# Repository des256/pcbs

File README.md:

# PCBs

Making electronics as well

## Prerequisites

KiCad 10.0
install plugin: impart GUI for KiCad
install plugin: Fabrication Toolkit
install plugin: wDark Theme
install repository: CD_FER's KiCad repository (https://raw.githubusercontent.com/CDFER/cd_fer-kicad-repository/main/repository.json)
install plugin: JLCPCB: KiCad Library

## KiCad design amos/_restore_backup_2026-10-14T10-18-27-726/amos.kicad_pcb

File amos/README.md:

# Amos

Jetson helper board (USB3 + 12V RS-485 Servo + 5V UART Servo)

Input Power: 19V laptop
Output Power: 19V jetson + 12V (10A..20A) servo + 5V (5A..10A) servo + 5V (5A) USB

Upstream USB Hub: USB3-C
Downstream USB Hub: 3x USB3-A + 1x internal to CH344Q

each servo bus either 12V 4-pin RS-485 or 5V 3-pin UART
selectable with DIP

## Schematic Sheets

2: Main Power + Jetson
3: Buck 12V 10A..20A
4: Buck 5V 5A..10A
5: Buck 5V USB
6: Buck 3V3 + 1V1
7: USB HUB
8: CH344Q
9: Servo A
10: Servo B
11: Servo C
12: Servo D
13: USB A
14: USB B
15: USB C

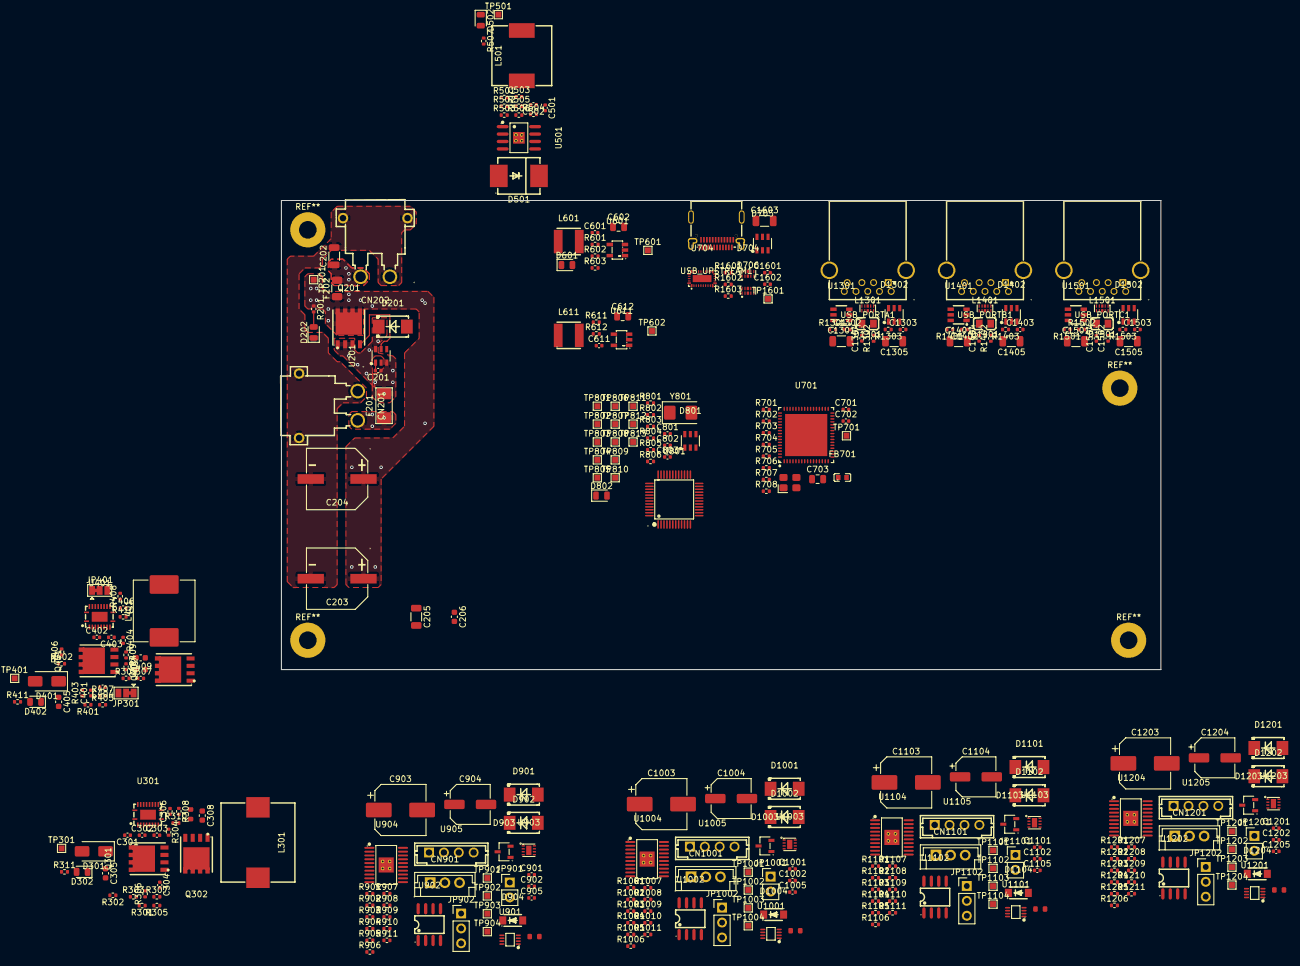
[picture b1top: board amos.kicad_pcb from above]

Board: 4 copper layers, 150.0 x 80.0 mm, 327 parts (0 on the bottom side), 216 nets.

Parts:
C201, C307, C407, C503, C803, C901, C902, C905, C1001, C1002, C1005, C1101, C1102, C1105, C1201, C1202, C1205, C1302, C1303, C1304, C1402, C1403, C1404, C1502, C1503, C1504, C1601, C1602: 100nF; C_0402_1005Metric
C202, C205: 10uF 50V; C_1206_3216Metric
C203, C204: 470uF 35V; CAP-SMD_BD10.0-L10.3-W10.3-LS11.3-FD
C206: 100nF 100V; C_0603_1608Metric
C301: 33nF; C_0402_1005Metric
C302, C502: 47pF; C_0402_1005Metric
C303: 3.3nF; C_0402_1005Metric
C304: 680pF; C_0402_1005Metric
C305, C405: 2.2uF; C_0603_1608Metric
C306: 10pF; C_0402_1005Metric
C308, C409: 100pF; C_0603_1608Metric
C401: 47nF; C_0402_1005Metric
C402: 150pF; C_0402_1005Metric
C403, C501: 4.7nF; C_0402_1005Metric
C404: 1.8nF; C_0402_1005Metric
C406: 15pF; C_0402_1005Metric
C601, C611: 6.8pF; C_0402_1005Metric
C602, C612: 22uF; C_0805_2012Metric
C701, C702: 30pF; C_0402_1005Metric
C703: 10uF; C_0805_2012Metric
C801, C802: 33pF; C_0402_1005Metric
C903, C1003, C1103, C1203: 470uF 25V; CP_Elec_8x10.5
C904, C1004, C1104, C1204: 470uF 10V; CP_Elec_6.3x7.7
C1301, C1401, C1501: 47uF 10V; C_1206_3216Metric
C1305, C1405, C1505, C1603: 1nF 2kV; C_1206_3216Metric
CN201: 19V INPUT; CONN-TH_XT30PW-M
CN202: 19V JETSON; CONN-TH_XT30PW-M
CN901, CN1001, CN1101, CN1201: B3B-EH-A; CONN-TH_B3B-EH-A-LF-SN
D201: SMBJ24A_C908801; SMB_L4.4-W3.6-LS5.3-RD
D202, D302, D402, D502, D601: LED Green; LED_0805_2012Metric
D301, D401: SS14; D_SMA
D501: B560C; SMC_L7.1-W6.2-LS8.1-RD
D704, D706, D1301, D1401, D1501: TPD4E05U06DQAR_C138714; USON-10_L2.5-W1.0-P0.50-BL
D705, D801, D1302, D1402, D1502: USBLC6-2SC6; SOT-23-6_L2.9-W1.6-P0.95-LS2.8-BL
D802: LED Yellow; LED_0805_2012Metric
D901, D1001, D1101, D1201: SMBJ13A; SMB_L4.4-W3.6-LS5.3-RD
D902, D1002, D1102, D1202: SMBJ6.0A; SMB_L4.4-W3.6-LS5.3-RD
D903, D1003, D1103, D1203: PSM712-LF-T7; SOT-23-3_L3.0-W1.7-P0.95-LS2.9-BR
D904, D1004, D1104, D1204: SMF5.0A; SOD-123FL_L2.8-W1.9-LS3.7-RD
F201: 15A T 2410; Fuse_2410_6125Metric
F202: 4A T 1206; Fuse_1206_3216Metric
FB701: BLM18PG221SN1D; L0603
JP301, JP401: SYNCIN GND OR PGOOD; SolderJumper-3_P1.3mm_Bridged12_Pad1.0x1.5mm
JP901, JP1001, JP1101, JP1201: RETRY; PinHeader_1x02_P2.54mm_Vertical
JP902, JP1002, JP1102, JP1202: 12=RS-485, 23=TTL; PinHeader_1x03_P2.54mm_Vertical
L301: 4.7uH 20A; IND-SMD_L13.5-W12.6
L401: 3.3uH 18A; L_Vishay_IHLP-4040
L501: 7.2uH 6A; IND-SMD_L10.2-W10.2_7447798720
L601, L611: 2.2uH 3.4A; IND-SMD_L4.0-W4.0_LQH44PN2R2MP0L
L1301, L1401, L1501: BLM21PG221SN1D; L0805
Q201, Q301, Q302, Q401, Q402: CSD18532Q5B; SON-8_L5.0-W6.0-P1.27-BL-1
R201, R703, R705, R706, R707, R708, R801, R911, R1011, R1111, R1211, R1301, R1401, R1501: 10k; R_0402_1005Metric
R301, R401, R611: 82k; R_0402_1005Metric
R302, R402: 7.5k; R_0402_1005Metric
R303: 24.9k; R_0402_1005Metric
R304: 15k; R_0402_1005Metric
R305: 2.37k; R_0402_1005Metric
R306: 200; R_0402_1005Metric
R307: 33.2k; R_0402_1005Metric
R308, R408: 20k; R_0402_1005Metric
R309, R409: 2.2; R_0402_1005Metric
R310: 240; R_0402_1005Metric
R311, R803, R804, R805, R806: 4.7k; R_0402_1005Metric
R312, R413: 2.2; R_0603
R403: 49.9; R_0402_1005Metric
R404: 11k; R_0402_1005Metric
R405: 23.2k; R_0402_1005Metric
R406, R411, R507, R603, R802: 1k; R_0402_1005Metric
R407: 4.42k; R_0402_1005Metric
R410: 150; R_0402_1005Metric
R501: 442k; R_0402_1005Metric
R502, R704: 90.9k; R_0402_1005Metric
R503: 243k; R_0402_1005Metric
R504, R1302, R1402, R1502: 16.9k; R_0402_1005Metric
R505: 53.6k; R_0402_1005Metric
R506: 10.2k; R_0402_1005Metric
R601: 453k; R_0402_1005Metric
R602, R612, R904, R906, R908, R909, R1004, R1006, R1008, R1009, R1104, R1106, R1108, R1109, R1204, R1206, R1208, R1209: 100k; R_0402_1005Metric
R701: 9.53k; R_0402_1005Metric
R702, R1303, R1403, R1503, R1602: 1M; R_0402_1005Metric
R901, R1001, R1101, R1201: 18.2k; R_0402_1005Metric
R902, R1002, R1102, R1202: 249k; R_0402_1005Metric
R903, R1003, R1103, R1203: 20.5k; R_0402_1005Metric
R905, R1005, R1105, R1205: 4.02k; R_0402_1005Metric
R907, R1007, R1107, R1207: 1.02k; R_0402_1005Metric
R910, R1010, R1110, R1210: 22; R_0402_1005Metric
R912, R1012, R1112, R1212: 120; R_0603
R1601: 910k; R_0402_1005Metric
R1603: 200k; R_0402_1005Metric
TP201: +19V; TestPoint_Pad_1.0x1.0mm
TP301: +12V_SERVO; TestPoint_Pad_1.0x1.0mm
TP401: +5V_SERVO; TestPoint_Pad_1.0x1.0mm
TP501: +5V_USB; TestPoint_Pad_1.0x1.0mm
TP601: +3V3; TestPoint_Pad_1.0x1.0mm
TP602: +1V1; TestPoint_Pad_1.0x1.0mm
TP701: GRSTz; TestPoint_Pad_1.0x1.0mm
TP801: RESET; TestPoint_Pad_1.0x1.0mm
TP802: SERVOB_TXD; TestPoint_Pad_1.0x1.0mm
TP803: SERVOB_RXD; TestPoint_Pad_1.0x1.0mm
TP804: SERVOB_TNOW; TestPoint_Pad_1.0x1.0mm
TP805: SERVOC_TXD; TestPoint_Pad_1.0x1.0mm
TP806: SERVOC_RXD; TestPoint_Pad_1.0x1.0mm
TP807: SERVOC_TNOW; TestPoint_Pad_1.0x1.0mm
TP808: SERVOD_TXD; TestPoint_Pad_1.0x1.0mm
TP809: SERVOD_RXD; TestPoint_Pad_1.0x1.0mm
TP810: SERVOD_TNOW; TestPoint_Pad_1.0x1.0mm
TP811: SERVOA_TXD; TestPoint_Pad_1.0x1.0mm
TP812: SERVOA_RXD; TestPoint_Pad_1.0x1.0mm
TP813: SERVOA_TNOW; TestPoint_Pad_1.0x1.0mm
TP901, TP1001, TP1101, TP1201: SHDN; TestPoint_Pad_1.0x1.0mm
TP902, TP1002, TP1102, TP1202: RS485 A; TestPoint_Pad_1.0x1.0mm
TP903, TP1003, TP1103, TP1203: TTL DATA; TestPoint_Pad_1.0x1.0mm
TP904, TP1004, TP1104, TP1204: RS485 B; TestPoint_Pad_1.0x1.0mm
TP1601: DIR; TestPoint_Pad_1.0x1.0mm
U201: LM74700QDBVTQ1; SOT-23-6_L2.9-W1.6-P0.95-LS2.8-TL
U301, U401: LM5145RGYR; VQFN-20_L4.5-W3.5-P0.50-BL-EP
U501: TPS54560DDAR; SOIC-8_L5.0-W4.0-P1.27-LS6.0-BL-EP2.0
U601, U611: TLV62569DBVR; SOT-23-5_L3.0-W1.7-P0.95-LS2.8-BR
U701: TUSB8041IRGCR; QFN-64_L9.0-W9.0-P0.50-BL-EP7.2
U704: HD3SS3220RNHR; WQFN-30_L4.5-W2.5-P0.4-BL-EP
U801: CH344Q_C2988084; LQFP-48_L7.0-W7.0-P0.50-LS9.0-BL
U901, U1001, U1101, U1201: SN74LVC2G241DCU; VSSOP-8_L2.3-W2.0-P0.50-LS3.1-BR
U902, U1002, U1102, U1202: SP3485EN-L/TR; SOIC-8_L5.0-W4.0-P1.27-LS6.0-BL
U903, U1003, U1103, U1203: TPS259531DSGR; WSON-8_L2.0-W2.0-P0.50-TL-EP
U904, U1004, U1104, U1204: TPS16630PWPR; HTSSOP-20_L6.5-W4.4-P0.65-LS6.4-TL-EP2.58
U905, U1005, U1105, U1205: B4B-EH-A; CONN-TH_B4B-EH-A-LF-SN
U1301, U1401, U1501: TPS2553DBVR; SOT-23-6_L2.9-W1.6-P0.95-LS2.8-BR
USB_PORTA1: HC-ST-003-01-J; USB-3.0-A-TH_HC-ST-003-01-Z
USB_PORTB1: HC-ST-003-01-J; USB-3.0-A-TH_HC-ST-003-01-Z
USB_PORTC1: HC-ST-003-01-J; USB-3.0-A-TH_HC-ST-003-01-Z
USB_UPSTREAM1: TYPE-C 24P QT; USB-C-SMD_TYPE-C-24P-QT
Y701: 24MHz 18pF; OSC-SMD_4P-L3.2-W2.5-BL
Y801: 8MHz 20pF; Crystal_SMD_5032-2Pin_5.0x3.2mm

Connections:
+1V1: C611.2, C612.1, FB701.2, L611.2, R611.2, TP602.1 (1_1), U701.5 (VDD), U701.8 (VDD), U701.13 (VDD), U701.21 (VDD), U701.28 (VDD), U701.31 (VDD)
+3V3: C601.2, C602.1, D801.5, L601.2, R601.2, R603.1, R703.2, R706.1, R707.2, R708.2, R801.1, R802.2, R908.1, R909.1, R911.2, R1008.1, R1009.1, R1011.2, R1108.1, R1109.1, R1111.2, R1208.1, R1209.1, R1211.2, R1301.2, R1401.2, R1501.2, R1601.1, R1603.1, TP601.1 (1_1), U701.16 (VDD33), U701.34 (VDD33), U701.52 (VDD33), U701.63 (VDD33), U704.8 (VCC33), U801.9 (VCC), U801.24 (VCC), U801.36 (VCC), U801.48 (VCC), U901.8 (VCC), U902.8 (VCC), U1001.8 (VCC), U1002.8 (VCC), U1101.8 (VCC), U1102.8 (VCC), U1201.8 (VCC), U1202.8 (VCC)
+5V_SERVO: D401.2 (A), L401.2, R405.1, R406.1, R411.1, R906.2, R1006.2, R1106.2, R1206.2, TP401.1 (1_1), U903.3 (IN), U903.4 (IN), U1003.3 (IN), U1003.4 (IN), U1103.3 (IN), U1103.4 (IN), U1203.3 (IN), U1203.4 (IN)
+5V_USB: D705.5, L501.2, R505.2, R507.2, TP501.1 (1_1), U601.1 (EN), U601.4 (VIN), U611.1 (EN), U611.4 (VIN), U704.30 (VDD5), U1301.1 (IN), U1401.1 (IN), U1501.1 (IN), USB_UPSTREAM1.A4 (VBUS), USB_UPSTREAM1.A9 (VBUS), USB_UPSTREAM1.B4 (VBUS), USB_UPSTREAM1.B9 (VBUS)
+12V_SERVO: D301.2 (A), L301.2, R306.1, R307.1, R311.1, R902.1, R904.1, R1002.1, R1004.1, R1102.1, R1104.1, R1202.1, R1204.1, TP301.1 (1_1), U904.1 (IN), U904.2 (IN), U904.3 (IN), U904.6 (P_IN), U1004.1 (IN), U1004.2 (IN), U1004.3 (IN), U1004.6 (P_IN), U1104.1 (IN), U1104.2 (IN), U1104.3 (IN), U1104.6 (P_IN), U1204.1 (IN), U1204.2 (IN), U1204.3 (IN), U1204.6 (P_IN)
+19V: C203.1, C204.1, C205.1, C206.1, F202.1, Q201.5 (D), Q201.6 (D), Q201.7 (D), Q201.8 (D), Q201.9 (EP), Q301.5 (D), Q301.6 (D), Q301.7 (D), Q301.8 (D), Q301.9 (EP), Q401.5 (D), Q401.6 (D), Q401.7 (D), Q401.8 (D), Q401.9 (EP), R201.1, R301.1, R401.1, R501.1, TP201.1 (1_1), U201.4 (CATHODE), U301.20 (VIN), U401.20 (VIN), U501.2 (VIN)
/Servo Bus A/SERVOA_RXD: U901.6 (1Y), U902.1 (RO)
/Servo Bus A/SERVOA_TNOW: JP902.2 (C), U901.7 (2OE), U902.3 (DE)
/Servo Bus A/SERVOA_TXD: U901.5 (2A), U902.4 (DI)
/Servo Bus B/SERVOB_RXD: U1001.6 (1Y), U1002.1 (RO)
/Servo Bus B/SERVOB_TNOW: JP1002.2 (C), U1001.7 (2OE), U1002.3 (DE)
/Servo Bus B/SERVOB_TXD: U1001.5 (2A), U1002.4 (DI)
/Servo Bus C/SERVOC_RXD: U1101.6 (1Y), U1102.1 (RO)
/Servo Bus C/SERVOC_TNOW: JP1102.2 (C), U1101.7 (2OE), U1102.3 (DE)
/Servo Bus C/SERVOC_TXD: U1101.5 (2A), U1102.4 (DI)
/Servo Bus Controller/SERVOA_RXD: TP812.1 (1_1), U801.31 (RXD0)
/Servo Bus Controller/SERVOA_TNOW: R806.1, TP813.1 (1_1), U801.39 (TNOW0/GPIO8)
/Servo Bus Controller/SERVOA_TXD: TP811.1 (1_1), U801.30 (TXD0)
/Servo Bus Controller/SERVOB_RXD: TP803.1 (1_1), U801.13 (RXD1)
/Servo Bus Controller/SERVOB_TNOW: R803.1, TP804.1 (1_1), U801.18 (TNOW1/GPIO9)
/Servo Bus Controller/SERVOB_TXD: TP802.1 (1_1), U801.12 (TXD1)
/Servo Bus Controller/SERVOC_RXD: TP806.1 (1_1), U801.22 (RXD2)
/Servo Bus Controller/SERVOC_TNOW: R804.1, TP807.1 (1_1), U801.19 (TNOW2/GPIO10)
/Servo Bus Controller/SERVOC_TXD: TP805.1 (1_1), U801.21 (TXD2)
/Servo Bus Controller/SERVOD_RXD: TP809.1 (1_1), U801.38 (RXD3)
/Servo Bus Controller/SERVOD_TNOW: R805.1, TP810.1 (1_1), U801.34 (TNOW3/DTR3/GPIO11)
/Servo Bus Controller/SERVOD_TXD: TP808.1 (1_1), U801.37 (TXD3)
/Servo Bus D/SERVOD_RXD: U1201.6 (1Y), U1202.1 (RO)
/Servo Bus D/SERVOD_TNOW: JP1202.2 (C), U1201.7 (2OE), U1202.3 (DE)
/Servo Bus D/SERVOD_TXD: U1201.5 (2A), U1202.4 (DI)
/USB Hub/USBA_OVERCUR_N: R708.1, U701.46 (OVERCUR1z)
/USB Hub/USBB_OVERCUR_N: R707.1, U701.47 (OVERCUR2z)
/USB Hub/USBC_OVERCUR_N: R706.2, U701.44 (OVERCUR3z)
/USB Port A/USBA_OVERCUR_N: R1301.1, U1301.4 (/FAULT)
/USB Port A/USBA_SSRX_N: D1301.5 (D2-), USB_PORTA1.5 (StdA_SSRX-)
/USB Port A/USBA_SSRX_P: D1301.4 (D2+), USB_PORTA1.6 (StdA_SSRX+)
/USB Port B/USBB_OVERCUR_N: R1401.1, U1401.4 (/FAULT)
/USB Port B/USBB_SSRX_N: D1401.5 (D2-), USB_PORTB1.5 (StdA_SSRX-)
/USB Port B/USBB_SSRX_P: D1401.4 (D2+), USB_PORTB1.6 (StdA_SSRX+)
/USB Port C/USBC_OVERCUR_N: R1501.1, U1501.4 (/FAULT)
/USB Port C/USBC_SSRX_N: D1501.5 (D2-), USB_PORTC1.5 (StdA_SSRX-)
/USB Port C/USBC_SSRX_P: D1501.4 (D2+), USB_PORTC1.6 (StdA_SSRX+)
GND: C202.2, C203.2, C204.2, C205.2, C206.2, C301.2, C305.2, C306.2, C308.2, C401.1, C405.2, C406.2, C409.2, C501.1, C502.2, C602.2, C612.2, C701.1, C702.1, C703.2, C801.2, C802.2, C803.1, C901.2, C902.1, C903.2, C904.2, C905.1, C1001.2, C1002.1, C1003.2, C1004.2, C1005.1, C1101.2, C1102.1, C1103.2, C1104.2, C1105.1, C1201.2, C1202.1, C1203.2, C1204.2, C1205.1, C1301.1, C1302.1, C1305.2, C1401.1, C1402.1, C1405.2, C1501.1, C1502.1, C1505.2, C1603.1, CN201.1 (-), CN201.3, CN201.4, CN202.1 (-), CN202.3, CN202.4, CN901.1, CN1001.1, CN1101.1, CN1201.1, D201.2, D202.1 (K), D302.1 (K), D402.1 (K), D501.2 (A), D502.1 (K), D601.1 (K), D704.3 (GND), D704.8 (GND), D705.2, D706.3 (GND), D706.8 (GND), D801.2, D901.2, D902.2, D903.3 (K), D904.2, D1001.2, D1002.2, D1003.3 (K), D1004.2, D1101.2, D1102.2, D1103.3 (K), D1104.2, D1201.2, D1202.2, D1203.3 (K), D1204.2, D1301.3 (GND), D1301.8 (GND), D1302.2, D1401.3 (GND), D1401.8 (GND), D1402.2, D1501.3 (GND), D1501.8 (GND), D1502.2, JP301.1 (A), JP401.1 (A), JP901.2 (B), JP1001.2 (B), JP1101.2 (B), JP1201.2 (B), Q302.1 (S), Q302.2 (S), Q302.3 (S), Q402.1 (S), Q402.2 (S), Q402.3 (S), R302.2, R303.1, R305.2, R402.1, R403.1, R407.1, R502.2, R503.2, R506.2, R602.1, R612.1, R701.2, R705.2, R803.2, R804.2, R805.2, R806.2, R903.2, R905.2, R907.1, R1003.2, R1005.2, R1007.1, R1103.2, R1105.2, R1107.1, R1203.2, R1205.2, R1207.1, R1302.2, R1303.2, R1402.2, R1403.2, R1502.2, R1503.2, R1602.2, U301.6 (AGND), U301.12 (PGND), U301.15 (EP), U301.21 (EP), U401.6 (AGND), U401.12 (PGND), U401.15 (EP), U401.21 (EP), U501.7 (GND), U501.9 (EP), U601.2 (GND), U611.2 (GND), U701.49 (TEST), U701.65 (VSS), U704.3 (CURRENT_MODE), U704.4 (PORT), U704.12 (ENn_MUX), U704.13 (GND), U704.28 (GND), U704.29 (ENn_CC), U704.31 (EP), U801.8 (GND), U801.20 (GND), U801.23 (GND), U801.35 (GND), U801.44 (TEST), U801.47 (GND), U901.4 (GND), U902.5 (GND), U903.8 (GND), U903.9 (GND), U904.9 (GND), U904.21 (EP), U905.1, U1001.4 (GND), U1002.5 (GND), U1003.8 (GND), U1003.9 (GND), U1004.9 (GND), U1004.21 (EP), U1005.1, U1101.4 (GND), U1102.5 (GND), U1103.8 (GND), U1103.9 (GND), U1104.9 (GND), U1104.21 (EP), U1105.1, U1201.4 (GND), U1202.5 (GND), U1203.8 (GND), U1203.9 (GND), U1204.9 (GND), U1204.21 (EP), U1205.1, U1301.2 (GND), U1401.2 (GND), U1501.2 (GND), USB_PORTA1.4 (GND), USB_PORTA1.7 (GND_DRAIN), USB_PORTB1.4 (GND), USB_PORTB1.7 (GND_DRAIN), USB_PORTC1.4 (GND), USB_PORTC1.7 (GND_DRAIN), USB_UPSTREAM1.A1 (GND), USB_UPSTREAM1.A12 (GND), USB_UPSTREAM1.B1 (GND), USB_UPSTREAM1.B12 (GND), Y701.2 (GND), Y701.4 (GND)
unnamed: C303.2, R304.1
unnamed: C304.1, R306.2
unnamed: C307.1, R309.2
unnamed: C308.1, R312.2
unnamed: C403.1, R404.1
unnamed: C404.2, R406.2
unnamed: C407.1, R409.2
unnamed: C409.1, R413.2
unnamed: C501.2, R504.2
unnamed: C902.2, C903.1, D901.1, U904.18 (OUT), U904.19 (OUT), U904.20 (OUT), U905.2
unnamed: C1002.2, C1003.1, D1001.1, U1004.18 (OUT), U1004.19 (OUT), U1004.20 (OUT), U1005.2
unnamed: C1102.2, C1103.1, D1101.1, U1104.18 (OUT), U1104.19 (OUT), U1104.20 (OUT), U1105.2
unnamed: C1202.2, C1203.1, D1201.1, U1204.18 (OUT), U1204.19 (OUT), U1204.20 (OUT), U1205.2
unnamed: C1305.1, R1303.1, USB_PORTA1.10 (SHELL), USB_PORTA1.11 (SHELL)
unnamed: C1405.1, R1403.1, USB_PORTB1.10 (SHELL), USB_PORTB1.11 (SHELL)
unnamed: C1505.1, R1503.1, USB_PORTC1.10 (SHELL), USB_PORTC1.11 (SHELL)
unnamed: C1603.2, R1602.1, USB_UPSTREAM1.3 (EP), USB_UPSTREAM1.4 (EP), USB_UPSTREAM1.25 (EP)
unnamed: CN201.2 (+), F201.1
unnamed: C202.1, CN202.2 (+), F202.2
unnamed: CN901.3, D904.1, R910.2, R911.1, TP903.1 (1_1)
unnamed: CN1001.3, D1004.1, R1010.2, R1011.1, TP1003.1 (1_1)
unnamed: CN1101.3, D1104.1, R1110.2, R1111.1, TP1103.1 (1_1)
unnamed: CN1201.3, D1204.1, R1210.2, R1211.1, TP1203.1 (1_1)
unnamed: D202.2 (A), R201.2
unnamed: C305.1, D301.1 (K), JP301.3 (B), R308.1, U301.14 (VCC)
unnamed: D302.2 (A), R311.2
unnamed: C405.1, D401.1 (K), JP401.3 (B), R408.1, U401.14 (VCC)
unnamed: D402.2 (A), R411.2
unnamed: C503.2, D501.1 (K), L501.1, U501.8 (SW)
unnamed: D502.2 (A), R507.1
unnamed: D601.2 (A), R603.2
unnamed: D704.1 (D1+), U704.21 (TX2p), USB_UPSTREAM1.B2 (TX2+)
unnamed: D704.2 (D1-), U704.20 (TX2n), USB_UPSTREAM1.B3 (TX2-)
unnamed: D704.4 (D2+), U704.19 (RX2p), USB_UPSTREAM1.A11 (RX2+)
unnamed: D704.5 (D2-), U704.18 (RX2n), USB_UPSTREAM1.A10 (RX2-)
unnamed: D705.1, USB_UPSTREAM1.A6 (D+), USB_UPSTREAM1.B6 (D+)
unnamed: D705.3, USB_UPSTREAM1.A7 (D-), USB_UPSTREAM1.B7 (D-)
unnamed: D706.1 (D1+), U704.17 (TX1p), USB_UPSTREAM1.A2 (TX1+)
unnamed: D706.2 (D1-), U704.16 (TX1n), USB_UPSTREAM1.A3 (TX1-)
unnamed: D706.4 (D2+), U704.15 (RX1p), USB_UPSTREAM1.B11 (RX1+)
unnamed: D706.5 (D2-), U704.14 (RX1n), USB_UPSTREAM1.B10 (RX1-)
unnamed: D802.2 (A), R802.1
unnamed: D802.1 (K), U801.14 (ACT)
unnamed: C1303.1, D1301.1 (D1+), USB_PORTA1.9 (StdA_SSTX+)
unnamed: C1304.2, D1301.2 (D1-), USB_PORTA1.8 (StdA_SSTX-)
unnamed: C1403.1, D1401.1 (D1+), USB_PORTB1.9 (StdA_SSTX+)
unnamed: C1404.2, D1401.2 (D1-), USB_PORTB1.8 (StdA_SSTX-)
unnamed: C1503.1, D1501.1 (D1+), USB_PORTC1.9 (StdA_SSTX+)
unnamed: C1504.2, D1501.2 (D1-), USB_PORTC1.8 (StdA_SSTX-)
unnamed: FB701.1, U701.51 (VDD), U701.57 (VDD)
unnamed: JP301.2 (C), U301.8 (SYNCIN)
unnamed: JP401.2 (C), U401.8 (SYNCIN)
unnamed: JP901.1 (A), U904.12 (MODE)
unnamed: JP902.1 (A), R909.2, U902.2 (~RE)
unnamed: JP902.3 (B), R908.2, U901.1 (~1OE)
unnamed: JP1001.1 (A), U1004.12 (MODE)
unnamed: JP1002.1 (A), R1009.2, U1002.2 (~RE)
unnamed: JP1002.3 (B), R1008.2, U1001.1 (~1OE)
unnamed: JP1101.1 (A), U1104.12 (MODE)
unnamed: JP1102.1 (A), R1109.2, U1102.2 (~RE)
unnamed: JP1102.3 (B), R1108.2, U1101.1 (~1OE)
unnamed: JP1201.1 (A), U1204.12 (MODE)
unnamed: JP1202.1 (A), R1209.2, U1202.2 (~RE)
unnamed: JP1202.3 (B), R1208.2, U1201.1 (~1OE)
unnamed: Q201.4 (G), U201.5 (GATE)
unnamed: Q301.4 (G), U301.18 (HO)
unnamed: C307.2, L301.1, Q301.1 (S), Q301.2 (S), Q301.3 (S), Q302.5 (D), Q302.6 (D), Q302.7 (D), Q302.8 (D), Q302.9 (EP), R310.2, R312.1, U301.19 (SW)
unnamed: Q302.4 (G), U301.13 (LO)
unnamed: Q401.4 (G), U401.18 (HO)
unnamed: C407.2, L401.1, Q401.1 (S), Q401.2 (S), Q401.3 (S), Q402.5 (D), Q402.6 (D), Q402.7 (D), Q402.8 (D), Q402.9 (EP), R410.2, R413.1, U401.19 (SW)
unnamed: Q402.4 (G), U401.13 (LO)
unnamed: C201.1, D201.1, F201.2, Q201.1 (S), Q201.2 (S), Q201.3 (S), U201.3 (EN), U201.6 (ANODE)
unnamed: C201.2, U201.1 (VCAP)
unnamed: R309.1, U301.17 (BST)
unnamed: C302.1, R304.2, U301.4 (COMP)
unnamed: R301.2, R302.1, U301.1 (EN/UVLO)
unnamed: C302.2, C303.1, C304.2, R305.1, R307.2, U301.5 (FB)
unnamed: C306.1, R310.1, U301.11 (ILIM)
unnamed: R308.2, U301.10 (PGOOD)
unnamed: R303.2, U301.2 (RT)
unnamed: C301.1, U301.3 (SS/TRK)
unnamed: R409.1, U401.17 (BST)
unnamed: C402.1, R404.2, U401.4 (COMP)
unnamed: R401.2, R402.2, U401.1 (EN/UVLO)
unnamed: C402.2, C403.2, C404.1, R405.2, R407.2, U401.5 (FB)
unnamed: C406.1, R410.1, U401.11 (ILIM)
unnamed: R408.2, U401.10 (PGOOD)
unnamed: R403.2, U401.2 (RT)
unnamed: C401.2, U401.3 (SS/TRK)
unnamed: C503.1, U501.1 (BOOT)
unnamed: C502.1, R504.1, U501.6 (COMP)
unnamed: R501.2, R502.1, U501.3 (EN)
unnamed: R505.1, R506.1, U501.5 (FB)
unnamed: R503.1, U501.4 (RT/CLK)
unnamed: C601.1, R601.1, R602.2, U601.5 (FB)
unnamed: L601.1, U601.3 (SW)
unnamed: C611.1, R611.1, R612.2, U611.5 (FB)
unnamed: L611.1, U611.3 (SW)
unnamed: C703.1, R703.1, TP701.1 (1_1), U701.50 (GRSTz)
unnamed: R701.1, U701.64 (USB_R1)
unnamed: R704.1, R705.1, U701.48 (USB_VBUS)
unnamed: C701.2, R702.1, U701.62 (XI), Y701.1 (OSC)
unnamed: C702.2, R702.2, U701.61 (XO), Y701.3 (OSC)
unnamed: U704.2 (CC1), USB_UPSTREAM1.A5 (CC1)
unnamed: U704.1 (CC2), USB_UPSTREAM1.B5 (CC2)
unnamed: R1603.2, TP1601.1 (1_1), U704.11 (DIR)
unnamed: C1602.2, U704.7 (TXn)
unnamed: C1601.2, U704.6 (TXp)
unnamed: R1601.2, U704.5 (VBUS_DET)
unnamed: C803.2, R801.2, TP801.1 (1_1), U801.7 (RESET)
unnamed: D801.1, U801.43 (UD+)
unnamed: D801.3, U801.42 (UD-)
unnamed: C801.1, U801.5 (XI), Y801.1
unnamed: C802.1, U801.6 (XO), Y801.2
unnamed: R910.1, U901.2 (1A), U901.3 (2Y)
unnamed: D903.1 (A1), R912.1, TP902.1 (1_1), U902.6 (A), U905.3
unnamed: D903.2 (A1), R912.2, TP904.1 (1_1), U902.7 (B), U905.4
unnamed: R906.1, U903.2 (EN/UVLO)
unnamed: R907.2, U903.7 (ILM)
unnamed: C904.1, C905.2, CN901.2, D902.1, U903.5 (OUT)
unnamed: R905.1, U904.11 (ILIM)
unnamed: R901.1, R902.2, R903.1, U904.8 (OVP)
unnamed: R901.2, U904.7 (UVLO)
unnamed: C901.1, U904.10 (dVdT)
unnamed: R904.2, TP901.1 (1_1), U904.13 (~SHDN)
unnamed: R1010.1, U1001.2 (1A), U1001.3 (2Y)
unnamed: D1003.1 (A1), R1012.1, TP1002.1 (1_1), U1002.6 (A), U1005.3
unnamed: D1003.2 (A1), R1012.2, TP1004.1 (1_1), U1002.7 (B), U1005.4
unnamed: R1006.1, U1003.2 (EN/UVLO)
unnamed: R1007.2, U1003.7 (ILM)
unnamed: C1004.1, C1005.2, CN1001.2, D1002.1, U1003.5 (OUT)
unnamed: R1005.1, U1004.11 (ILIM)
unnamed: R1001.1, R1002.2, R1003.1, U1004.8 (OVP)
unnamed: R1001.2, U1004.7 (UVLO)
unnamed: C1001.1, U1004.10 (dVdT)
unnamed: R1004.2, TP1001.1 (1_1), U1004.13 (~SHDN)
unnamed: R1110.1, U1101.2 (1A), U1101.3 (2Y)
unnamed: D1103.1 (A1), R1112.1, TP1102.1 (1_1), U1102.6 (A), U1105.3
unnamed: D1103.2 (A1), R1112.2, TP1104.1 (1_1), U1102.7 (B), U1105.4
unnamed: R1106.1, U1103.2 (EN/UVLO)
unnamed: R1107.2, U1103.7 (ILM)
unnamed: C1104.1, C1105.2, CN1101.2, D1102.1, U1103.5 (OUT)
unnamed: R1105.1, U1104.11 (ILIM)
unnamed: R1101.1, R1102.2, R1103.1, U1104.8 (OVP)
unnamed: R1101.2, U1104.7 (UVLO)
unnamed: C1101.1, U1104.10 (dVdT)
unnamed: R1104.2, TP1101.1 (1_1), U1104.13 (~SHDN)
unnamed: R1210.1, U1201.2 (1A), U1201.3 (2Y)
unnamed: D1203.1 (A1), R1212.1, TP1202.1 (1_1), U1202.6 (A), U1205.3
unnamed: D1203.2 (A1), R1212.2, TP1204.1 (1_1), U1202.7 (B), U1205.4
unnamed: R1206.1, U1203.2 (EN/UVLO)
unnamed: R1207.2, U1203.7 (ILM)
unnamed: C1204.1, C1205.2, CN1201.2, D1202.1, U1203.5 (OUT)
unnamed: R1205.1, U1204.11 (ILIM)
unnamed: R1201.1, R1202.2, R1203.1, U1204.8 (OVP)
unnamed: R1201.2, U1204.7 (UVLO)
unnamed: C1201.1, U1204.10 (dVdT)
unnamed: R1204.2, TP1201.1 (1_1), U1204.13 (~SHDN)
unnamed: R1302.1, U1301.5 (ILIM)
unnamed: C1301.2, L1301.1, U1301.6 (OUT)
unnamed: R1402.1, U1401.5 (ILIM)
unnamed: C1401.2, L1401.1, U1401.6 (OUT)
unnamed: R1502.1, U1501.5 (ILIM)
unnamed: C1501.2, L1501.1, U1501.6 (OUT)
unnamed: D1302.1, USB_PORTA1.3 (D+)
unnamed: D1302.3, USB_PORTA1.2 (D-)
unnamed: C1302.2, D1302.5, L1301.2, USB_PORTA1.1 (Vbus)
unnamed: D1402.1, USB_PORTB1.3 (D+)
unnamed: D1402.3, USB_PORTB1.2 (D-)
unnamed: C1402.2, D1402.5, L1401.2, USB_PORTB1.1 (Vbus)
unnamed: D1502.1, USB_PORTC1.3 (D+)
unnamed: D1502.3, USB_PORTC1.2 (D-)
unnamed: C1502.2, D1502.5, L1501.2, USB_PORTC1.1 (Vbus)
